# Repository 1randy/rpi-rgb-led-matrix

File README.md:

# rpi-rgb-led-matrix
Raspberry Pi &amp; Dot Matrix LED Displays

Additional stuff used with [hzeller LED matrix library & software](https://github.com/hzeller/rpi-rgb-led-matrix)

## PCB adapter for Raspberry Pi to Hub75 RGB Matrixes
==================================================

Since hand-wiring can be a little tedious, here are some PCBs that help
with the wiring when using the `rpi-rgb-led-matrix` code.

   * [DMD-RaspberryPi](./DMD-RaspberryPi) active adapter board <br>
     Supports three parallel chains with active buffering
     and 3.3V -> 5V level shifting for best reliability. Requires SMD soldering.<br>
     EAGLE 7.x files, added WAGO 2060 cable clamp for powering the RPI.

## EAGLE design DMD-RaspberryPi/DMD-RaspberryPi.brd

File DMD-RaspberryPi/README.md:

Adapter PCB to support up to 3 panel chains
===========================================

   * Supports up to three panel chains for newer plus models and
     Raspberry Pi 2 that have 40 GPIO pins.
   * Uses HCT245 to level shift signals from 3.3V to 5V and shield
     the Raspberry Pi GPIOs from overloading.
   * Optional: Pads to power the Pi with 5V, including optional capacitor footprints.
   * Provides a way to choose the pinout for different kinds of 64x64 matrixes.
   * BOM:
     - 4x 74HCT245 or 74AHCT245 in 20-SOIC, 7.5mm package which should make
     it easy to hand-solder. Make sure to get the variant with the **T**: HC**T** or AHC**T**
     (there are also HC or AHC, don't use these).
     - 4x 100nF ceramic capacitor (0805 package)
     - 1x 10kOhm resistor (0805 package). Not critcial, just a pullup (2.2k .. 15k probably ok).
     - 3x 16pin IDC (=2x8) male receptible to connect the panels.
     - 1x 40pin female connector to connect to the RPi.
     - 1x (optional) 22μF .. 100μF capacitor for 5V rail.
     - 1x (optional) WAGO 2060 Cable Clamp

## Layout
![pcb-top][pcb-top]
![pcb-bot][pcb-bot]

## Schematic

![Schematic][schematic]

[pcb-top]: ./DMD-RaspberryPi_pcb_top.jpg
[pcb-bot]: ./DMD-RaspberryPi_pcb_bot.jpg
[schematic]: ./DMD-RaspberryPi.sch.png

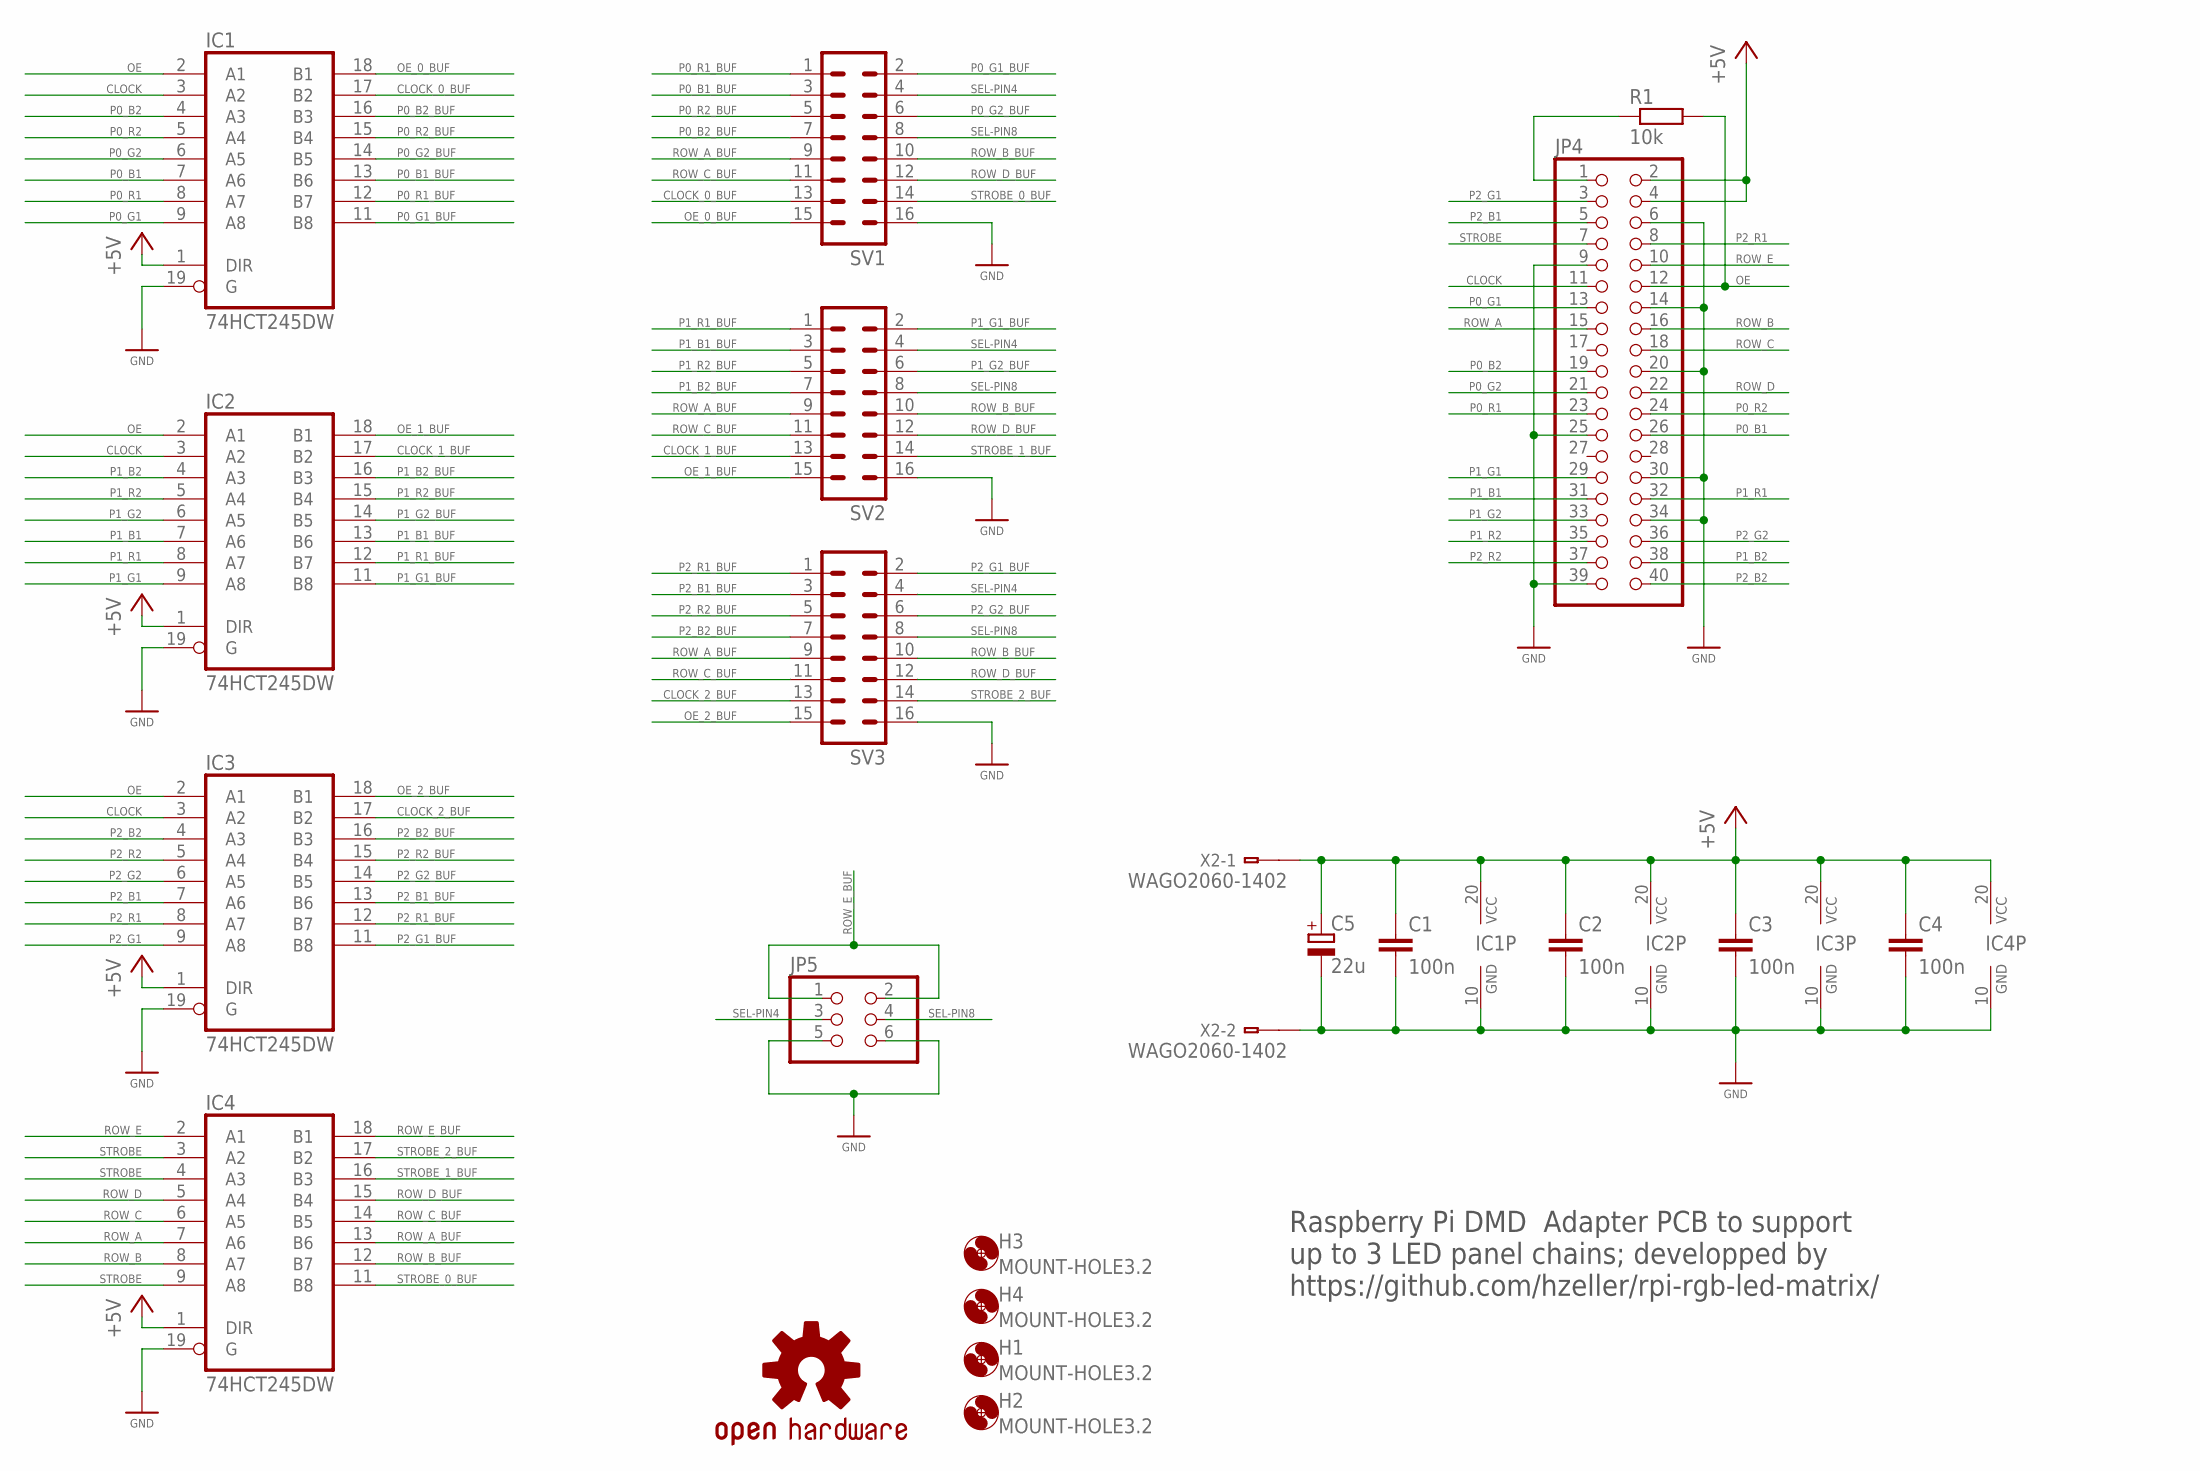
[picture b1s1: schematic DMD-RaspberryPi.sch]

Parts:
C1, C2, C3, C4: 100n; C0805
C5: 22u; PANASONIC_C
H1, H2, H3, H4: MOUNT-HOLE3.2; 3,2
IC1, IC2, IC3, IC4: 74HCT245DW; SO20W
JP4: PINHD-2X20; 2X20
JP5: PINHD-2X3; 2X03
LOGO1: OSHW-LOGOL-COPPER; OSHW-LOGO-L_COPPER
R1: 10k; R0805
SV1, SV2, SV3: ML16
X2: WAGO2060-1402; THT_RM4_2

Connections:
+5V: C1.1, C2.1, C3.1, C4.1, C5.+, IC1.1 (DIR), IC1.20 (VCC), IC2.1 (DIR), IC2.20 (VCC), IC3.1 (DIR), IC3.20 (VCC), IC4.1 (DIR), IC4.20 (VCC), JP4.2, JP4.4, X2.A2
CLOCK: IC1.3 (A2), IC2.3 (A2), IC3.3 (A2), JP4.11
CLOCK_0_BUF: IC1.17 (B2), SV1.13
CLOCK_1_BUF: IC2.17 (B2), SV2.13
CLOCK_2_BUF: IC3.17 (B2), SV3.13
GND: C1.2, C2.2, C3.2, C4.2, C5.-, IC1.10 (GND), IC1.19 (G), IC2.10 (GND), IC2.19 (G), IC3.10 (GND), IC3.19 (G), IC4.10 (GND), IC4.19 (G), JP4.6, JP4.9, JP4.14, JP4.20, JP4.25, JP4.30, JP4.34, JP4.39, JP5.5, JP5.6, SV1.16, SV2.16, SV3.16, X2.B2
unnamed: JP4.1, R1.1
OE: IC1.2 (A1), IC2.2 (A1), IC3.2 (A1), JP4.12, R1.2
OE_0_BUF: IC1.18 (B1), SV1.15
OE_1_BUF: IC2.18 (B1), SV2.15
OE_2_BUF: IC3.18 (B1), SV3.15
P0_B1: IC1.7 (A6), JP4.26
P0_B1_BUF: IC1.13 (B6), SV1.3
P0_B2: IC1.4 (A3), JP4.19
P0_B2_BUF: IC1.16 (B3), SV1.7
P0_G1: IC1.9 (A8), JP4.13
P0_G1_BUF: IC1.11 (B8), SV1.2
P0_G2: IC1.6 (A5), JP4.21
P0_G2_BUF: IC1.14 (B5), SV1.6
P0_R1: IC1.8 (A7), JP4.23
P0_R1_BUF: IC1.12 (B7), SV1.1
P0_R2: IC1.5 (A4), JP4.24
P0_R2_BUF: IC1.15 (B4), SV1.5
P1_B1: IC2.7 (A6), JP4.31
P1_B1_BUF: IC2.13 (B6), SV2.3
P1_B2: IC2.4 (A3), JP4.38
P1_B2_BUF: IC2.16 (B3), SV2.7
P1_G1: IC2.9 (A8), JP4.29
P1_G1_BUF: IC2.11 (B8), SV2.2
P1_G2: IC2.6 (A5), JP4.33
P1_G2_BUF: IC2.14 (B5), SV2.6
P1_R1: IC2.8 (A7), JP4.32
P1_R1_BUF: IC2.12 (B7), SV2.1
P1_R2: IC2.5 (A4), JP4.35
P1_R2_BUF: IC2.15 (B4), SV2.5
P2_B1: IC3.7 (A6), JP4.5
P2_B1_BUF: IC3.13 (B6), SV3.3
P2_B2: IC3.4 (A3), JP4.40
P2_B2_BUF: IC3.16 (B3), SV3.7
P2_G1: IC3.9 (A8), JP4.3
P2_G1_BUF: IC3.11 (B8), SV3.2
P2_G2: IC3.6 (A5), JP4.36
P2_G2_BUF: IC3.14 (B5), SV3.6
P2_R1: IC3.8 (A7), JP4.8
P2_R1_BUF: IC3.12 (B7), SV3.1
P2_R2: IC3.5 (A4), JP4.37
P2_R2_BUF: IC3.15 (B4), SV3.5
ROW_A: IC4.7 (A6), JP4.15
ROW_A_BUF: IC4.13 (B6), SV1.9, SV2.9, SV3.9
ROW_B: IC4.8 (A7), JP4.16
ROW_B_BUF: IC4.12 (B7), SV1.10, SV2.10, SV3.10
ROW_C: IC4.6 (A5), JP4.18
ROW_C_BUF: IC4.14 (B5), SV1.11, SV2.11, SV3.11
ROW_D: IC4.5 (A4), JP4.22
ROW_D_BUF: IC4.15 (B4), SV1.12, SV2.12, SV3.12
ROW_E: IC4.2 (A1), JP4.10
ROW_E_BUF: IC4.18 (B1), JP5.1, JP5.2
SEL-PIN4: JP5.3, SV1.4, SV2.4, SV3.4
SEL-PIN8: JP5.4, SV1.8, SV2.8, SV3.8
STROBE: IC4.3 (A2), IC4.4 (A3), IC4.9 (A8), JP4.7
STROBE_0_BUF: IC4.11 (B8), SV1.14
STROBE_1_BUF: IC4.16 (B3), SV2.14
STROBE_2_BUF: IC4.17 (B2), SV3.14

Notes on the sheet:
Raspberry Pi DMD Adapter PCB to support up to 3 LED panel chains; developped by https://github.com/hzeller/rpi-rgb-led-matrix/

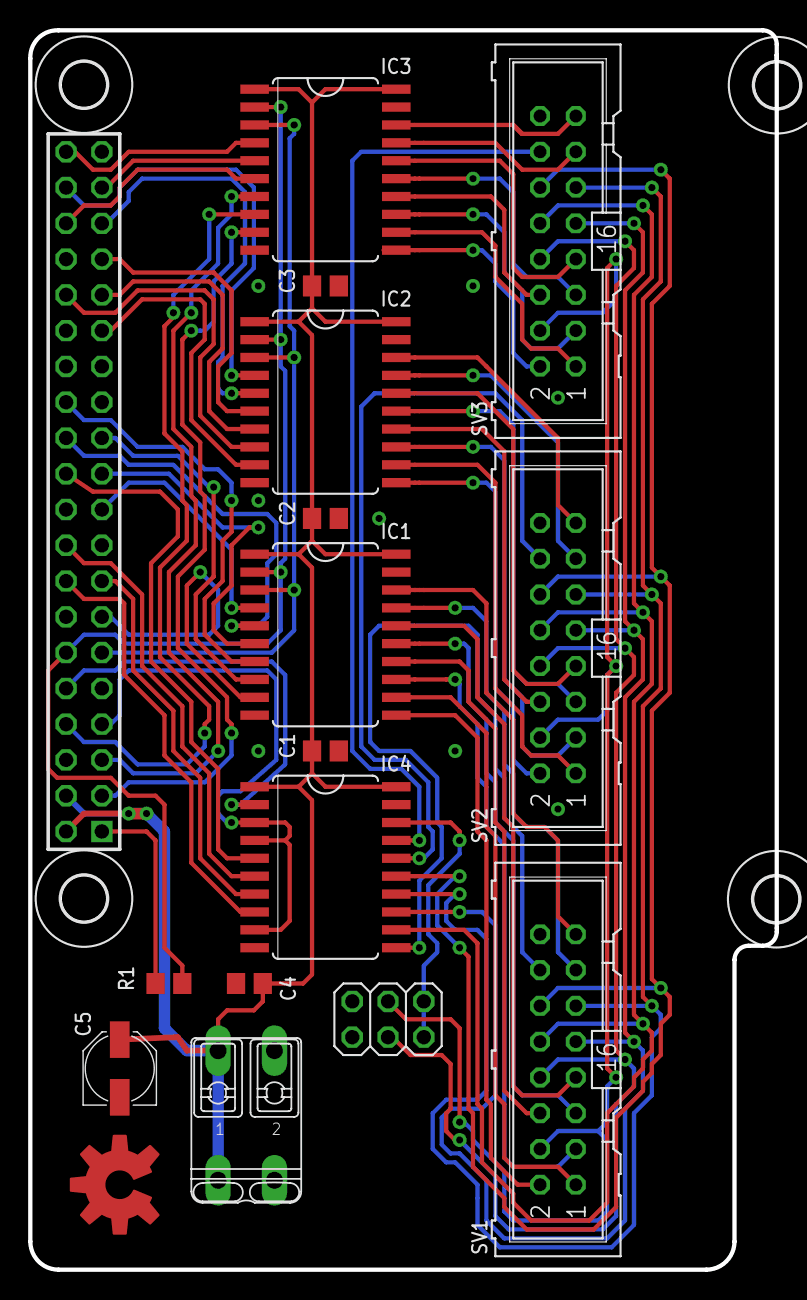
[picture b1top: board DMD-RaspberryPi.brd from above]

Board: 2 copper layers, 53.0 x 88.0 mm, 21 parts (0 on the bottom side), 63 nets.

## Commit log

2018-08-20 initial upload

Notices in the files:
parts and their libraries:
SparkFun-Aesthetics: Licensing: Creative Commons ShareAlike 4.0 International - https://creativecommons.org/licenses/by-sa/4.0
